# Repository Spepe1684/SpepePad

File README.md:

# SpepePad
my own macropad
It has 6 keys, 6 leds to light them up, a rotary encoder, and an oled display!
I made it as a way to introduce myself to basic hardware building skills like pcb design and CAD.

Here is my pcb layout.

Here is the kicad schematic
I have not finished teh CAD yet, but will update the repo ASAP!

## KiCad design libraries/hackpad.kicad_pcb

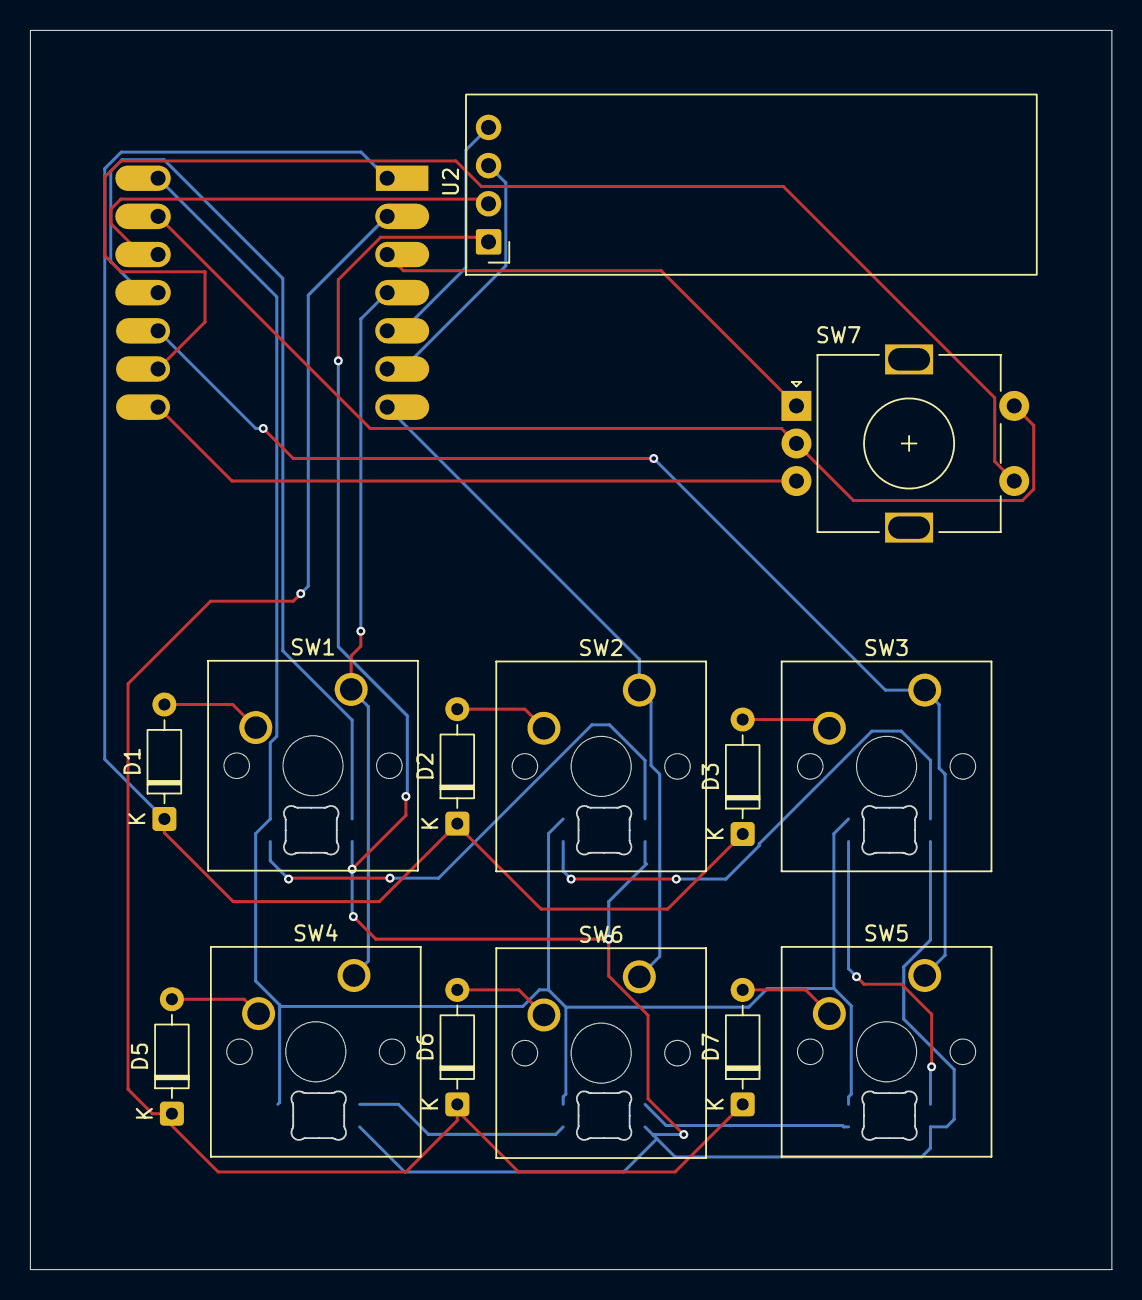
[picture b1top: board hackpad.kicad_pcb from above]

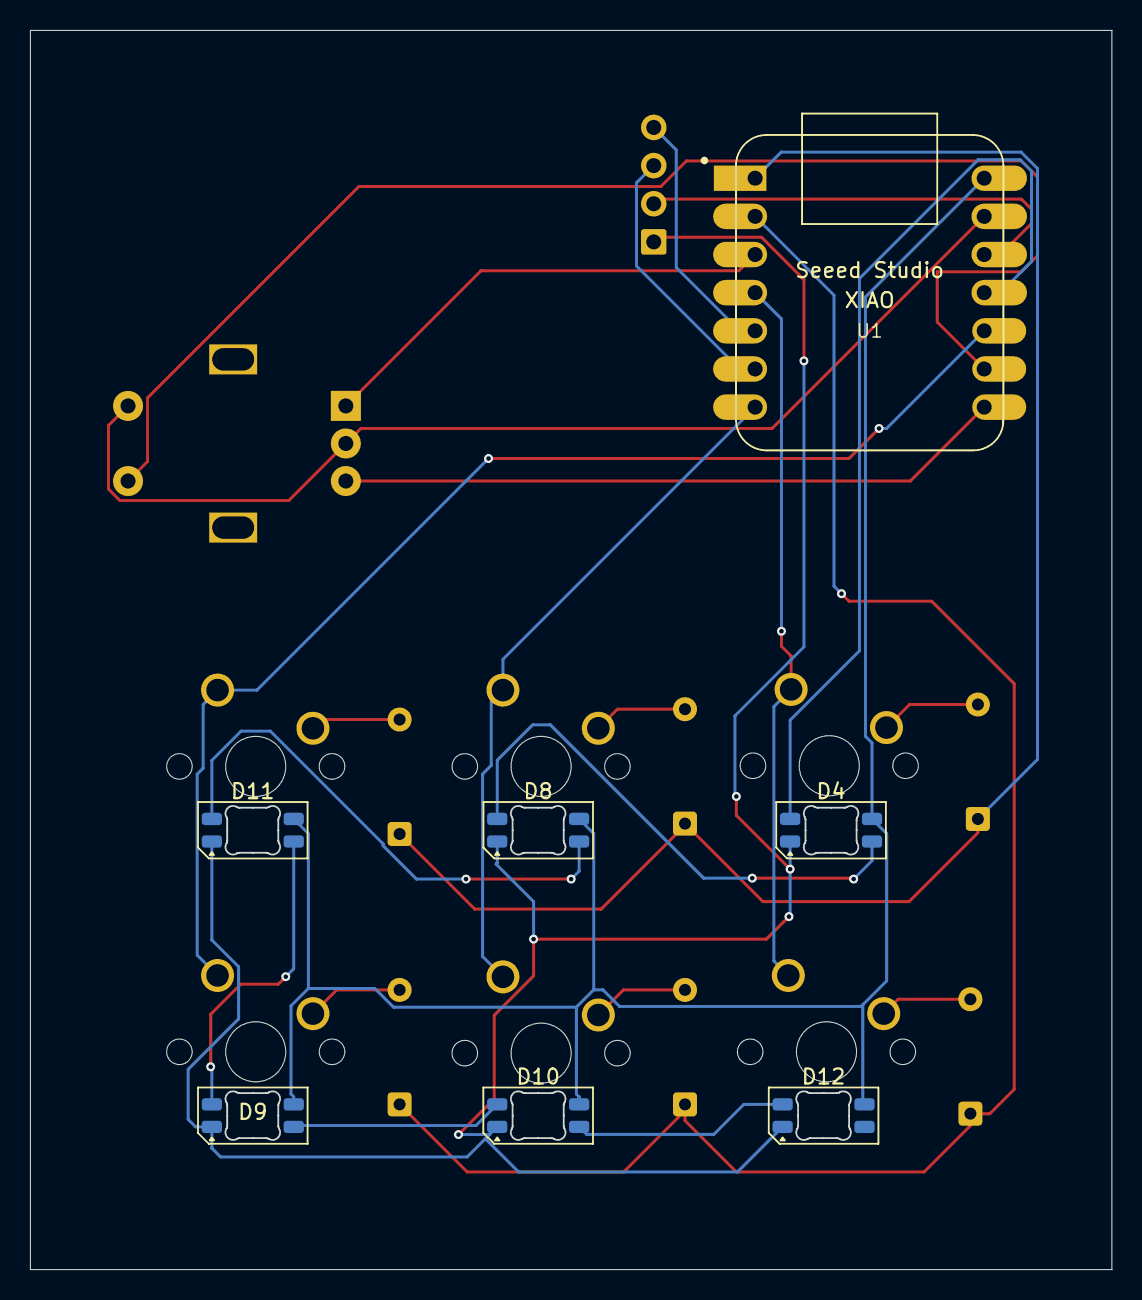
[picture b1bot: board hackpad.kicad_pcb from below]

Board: 2 copper layers, 72.0 x 82.5 mm, 21 parts (7 on the bottom side), 26 nets.

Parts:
D1, D2, D3, D5, D6, D7: 1N4148; D_DO-35_SOD27_P7.62mm_Horizontal
D4, D8, D9, D10, D11, D12: SK6812MINI-E; LED_SK6812MINI-E_3.2x2.8mm_P1.5mm_ReverseMount
SW1, SW2, SW3, SW4, SW5, SW6: SW_Push; SW_Cherry_MX_1.00u_PCB
SW7: RotaryEncoder_Switch; RotaryEncoder_Alps_EC11E-Switch_Vertical_H20mm
U1: MOUDLE-SEEEDUINO-XIAO; XIAO-Generic-Hybrid-14P-2.54-21X17.8MM
U2: ER_OLEDM0.91_1x-I2C

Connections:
3v: U1.12 (3V3), U2.2 (VCC)
+5V: D4.3 (VDD), D8.3 (VDD), D9.3 (VDD), D10.3 (VDD), D11.3 (VDD), D12.3 (VDD), U1.14 (5V)
GND: D4.1 (VSS), D8.1 (VSS), D9.1 (VSS), D10.1 (VSS), D11.1 (VSS), D12.1 (VSS), U2.1 (GND)
unnamed: D1.2 (A), SW1.2
unnamed: D2.2 (A), SW2.2
unnamed: D3.2 (A), SW3.2
unnamed: D4.4 (DOUT), D8.2 (DIN)
unnamed: D5.2 (A), SW4.2
unnamed: D6.2 (A), SW6.2
unnamed: D7.2 (A), SW5.2
unnamed: D9.4 (DOUT), D10.2 (DIN)
unnamed: D10.4 (DOUT), D12.2 (DIN)
unnamed: D8.4 (DOUT), D11.2 (DIN)
unnamed: D9.2 (DIN), D11.4 (DOUT)
column 0: SW1.1, SW4.1, U1.4 (PA11_A3_D3)
column 1: SW2.1, SW6.1, U1.7 (PB08_A6_D6_TX)
column 2: SW3.1, SW5.1, U1.10 (PA5_A9_D9_MISO)
d2: SW7.A, U1.3 (PA10_A2_D2)
d7: SW7.B, U1.8 (PB09_A7_D7_RX)
d8: SW7.S1, U1.9 (PA7_A8_D8_SCK)
gnd: SW7.C, SW7.S2, U1.13 (GND)
led: D4.2 (DIN), U1.11 (PA6_A10_D10_MOSI)
row 0: D1.1 (K), D2.1 (K), D3.1 (K), U1.1 (PA02_A0_D0)
row 1: D5.1 (K), D6.1 (K), D7.1 (K), U1.2 (PA4_A1_D1)
scl: U1.6 (PA9_A5_D5_SCL), U2.3 (SCL)
sda: U1.5 (PA8_A4_D4_SDA), U2.4 (SDA)
